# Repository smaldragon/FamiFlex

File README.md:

# FamiFlex

> Note: This project is currently in a prototype beta state, use at own risk

This is the repo for the FF1 (aka FamiFlex) famicom/famiclone homebrew mapper, more info is avaliable at:

https://smaldragon.github.io/blog/famiflex.html

* **kicad** - contains the original Kicad Files
* **python** - scripts to help with generating rom files for burning
* **gerbers** - `.zip` files for production with JLCPcb

## Changelog

### v0b

* Changed ROMS to smd PLCC sockets, to better fit cart shells
* Adjusted dimensions of PCB to better fit cart shells

### v0a

Initial Version

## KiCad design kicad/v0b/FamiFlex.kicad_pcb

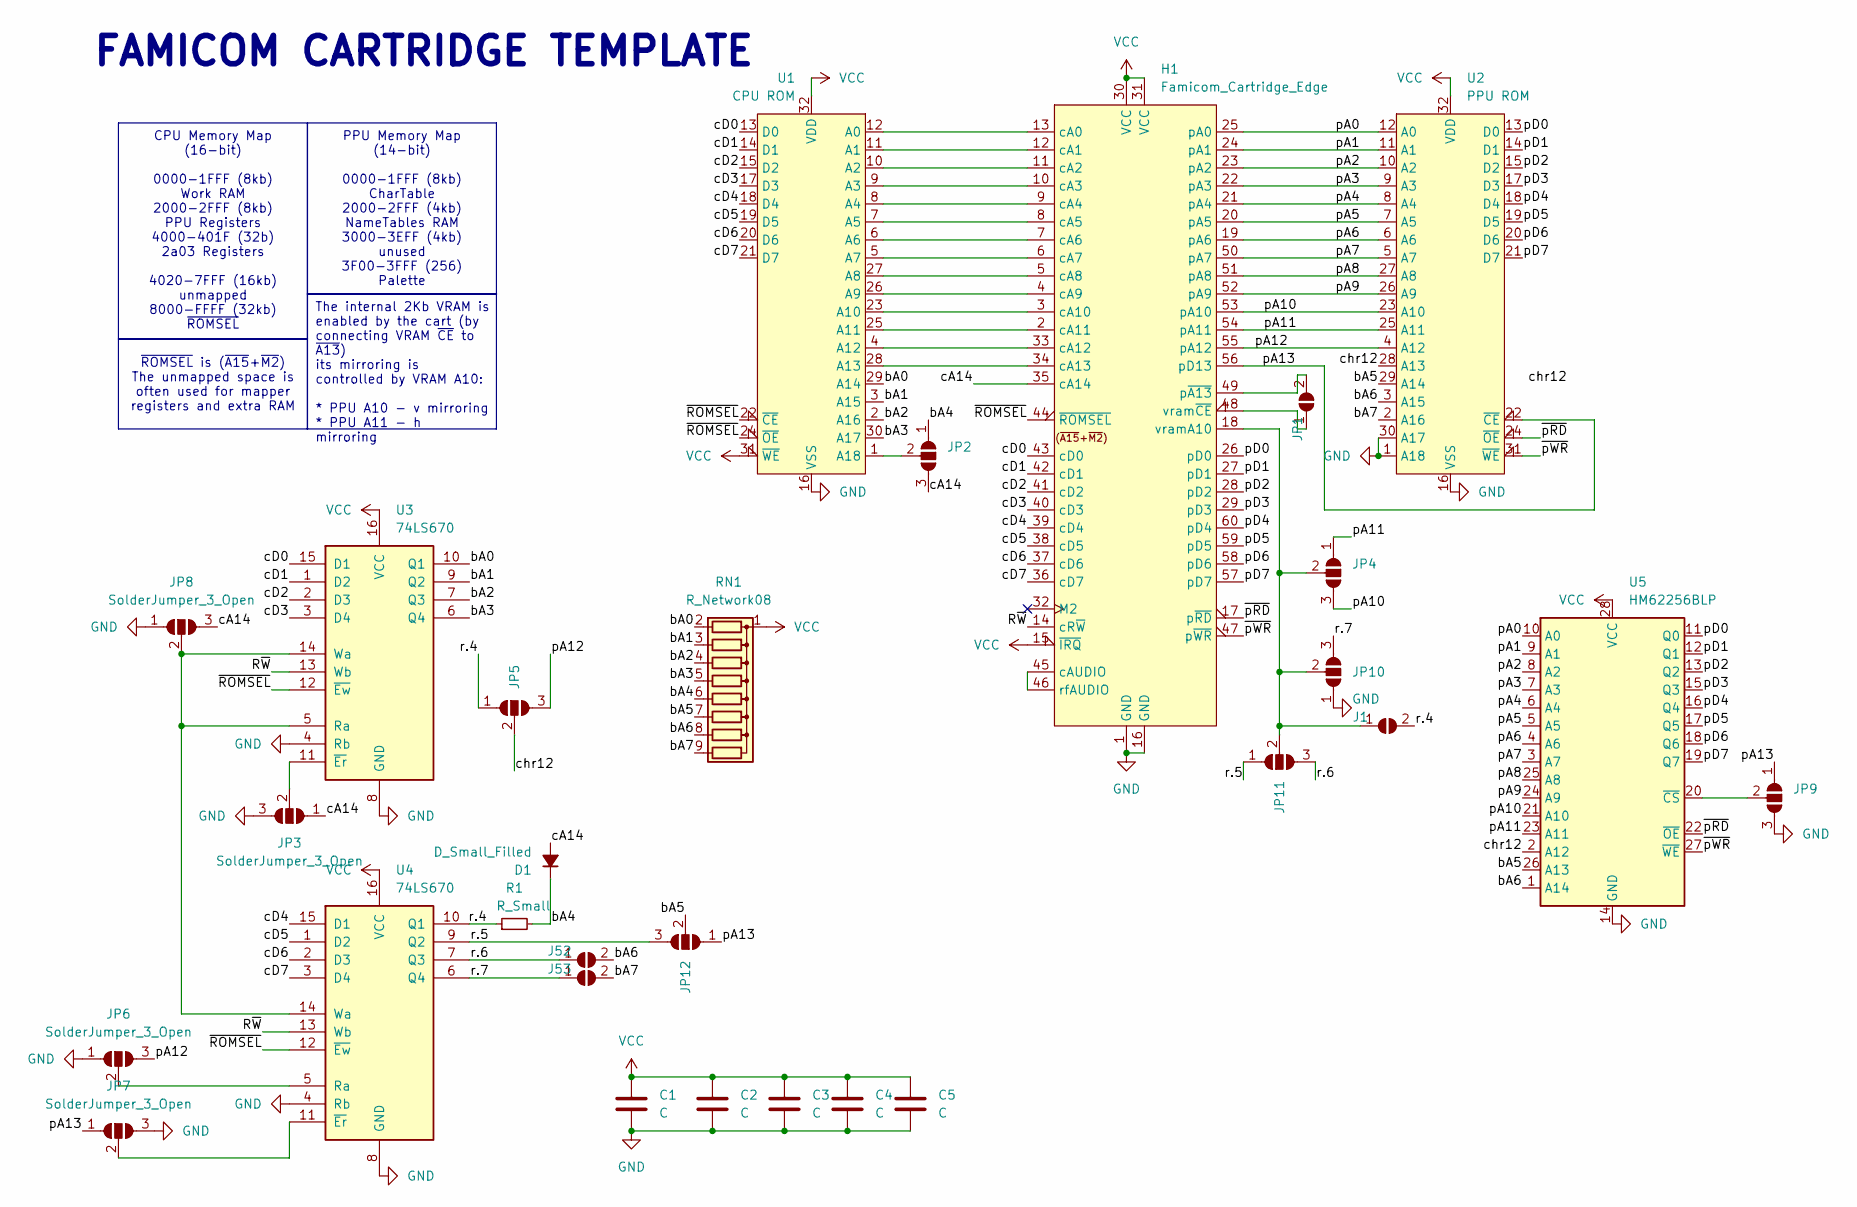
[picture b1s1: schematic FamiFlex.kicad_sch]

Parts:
C1, C2, C3, C4, C5: C; C_0805_2012Metric_Pad1.18x1.45mm_HandSolder
D1: D_Small_Filled; D_DO-41_SOD81_P2.54mm_Vertical_KathodeUp
H1: Famicom_Cartridge_Edge; Famicom Cartridge Edge Connector (long legs)
J1, J52, J53: SolderJumper_2_Open; SolderJumper-2_P1.3mm_Open_RoundedPad1.0x1.5mm
JP1: SolderJumper_2_Open; SolderJumper-2_P1.3mm_Open_RoundedPad1.0x1.5mm
JP2, JP3, JP4, JP5, JP6, JP7, JP8, JP9, JP10, JP11, JP12: SolderJumper_3_Open; SolderJumper-3_P1.3mm_Open_RoundedPad1.0x1.5mm
R1: R_Small; R_0805_2012Metric_Pad1.15x1.40mm_HandSolder
RN1: R_Network08; R_Array_SIP9
U1: CPU ROM; PLCC-32_SMD-Socket
U2: PPU ROM; PLCC-32_SMD-Socket
U3, U4: 74LS670; DIP-16_W7.62mm_Socket
U5: HM62256BLP; DIP-28_W15.24mm_Socket

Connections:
/R~W: H1.14 (cR~W), U3.13 (Wb), U4.13 (Wb)
/bA0: RN1.2 (R1), U1.29 (A14), U3.10 (Q1)
/bA1: RN1.3 (R2), U1.3 (A15), U3.9 (Q2)
/bA2: RN1.4 (R3), U1.2 (A16), U3.7 (Q3)
/bA3: RN1.5 (R4), U1.30 (A17), U3.6 (Q4)
/bA4: D1.1 (K), JP2.1 (A), R1.2, RN1.6 (R5)
/bA5: JP12.2 (C), RN1.7 (R6), U2.29 (A14), U5.26 (A13)
/bA6: J52.2 (B), RN1.8 (R7), U2.3 (A15), U5.1 (A14)
/bA7: J53.2 (B), RN1.9 (R8), U2.2 (A16)
/cA14: D1.2 (A), H1.35 (cA14), JP2.3 (B), JP3.1 (A), JP8.3 (B)
/cD0: H1.43 (cD0), U1.13 (D0), U3.15 (D1)
/cD1: H1.42 (cD1), U1.14 (D1), U3.1 (D2)
/cD2: H1.41 (cD2), U1.15 (D2), U3.2 (D3)
/cD3: H1.40 (cD3), U1.17 (D3), U3.3 (D4)
/cD4: H1.39 (cD4), U1.18 (D4), U4.15 (D1)
/cD5: H1.38 (cD5), U1.19 (D5), U4.1 (D2)
/cD6: H1.37 (cD6), U1.20 (D6), U4.2 (D3)
/cD7: H1.36 (cD7), U1.21 (D7), U4.3 (D4)
/chr12: JP5.2 (C), U2.28 (A13), U5.2 (A12)
/pA0: H1.25 (pA0), U2.12 (A0), U5.10 (A0)
/pA1: H1.24 (pA1), U2.11 (A1), U5.9 (A1)
/pA2: H1.23 (pA2), U2.10 (A2), U5.8 (A2)
/pA3: H1.22 (pA3), U2.9 (A3), U5.7 (A3)
/pA4: H1.21 (pA4), U2.8 (A4), U5.6 (A4)
/pA5: H1.20 (pA5), U2.7 (A5), U5.5 (A5)
/pA6: H1.19 (pA6), U2.6 (A6), U5.4 (A6)
/pA7: H1.50 (pA7), U2.5 (A7), U5.3 (A7)
/pA8: H1.51 (pA8), U2.27 (A8), U5.25 (A8)
/pA9: H1.52 (pA9), U2.26 (A9), U5.24 (A9)
/pA10: H1.53 (pA10), JP4.3 (B), U2.23 (A10), U5.21 (A10)
/pA11: H1.54 (pA11), JP4.1 (A), U2.25 (A11), U5.23 (A11)
/pA12: H1.55 (pA12), JP5.3 (B), JP6.3 (B), U2.4 (A12)
/pA13: H1.56 (pD13), JP7.1 (A), JP9.1 (A), JP12.1 (A), U2.22 (~CE)
/pD0: H1.26 (pD0), U2.13 (D0), U5.11 (Q0)
/pD1: H1.27 (pD1), U2.14 (D1), U5.12 (Q1)
/pD2: H1.28 (pD2), U2.15 (D2), U5.13 (Q2)
/pD3: H1.29 (pD3), U2.17 (D3), U5.15 (Q3)
/pD4: H1.60 (pD4), U2.18 (D4), U5.16 (Q4)
/pD5: H1.59 (pD5), U2.19 (D5), U5.17 (Q5)
/pD6: H1.58 (pD6), U2.20 (D6), U5.18 (Q6)
/pD7: H1.57 (pD7), U2.21 (D7), U5.19 (Q7)
/r.4: J1.2 (B), JP5.1 (A), R1.1, U4.10 (Q1)
/r.5: JP11.1 (A), JP12.3 (B), U4.9 (Q2)
/r.6: J52.1 (A), JP11.3 (B), U4.7 (Q3)
/r.7: J53.1 (A), JP10.3 (B), U4.6 (Q4)
/~ROMSEL: H1.44 (~ROMSEL), U1.22 (~CE), U1.24 (~OE), U3.12 (~Ew), U4.12 (~Ew)
/~pRD: H1.17 (p~RD), U2.24 (~OE), U5.22 (~OE)
/~pWR: H1.47 (p~WR), U2.31 (~WE), U5.27 (~WE)
GND: C1.2, C2.2, C3.2, C4.2, C5.2, H1.1 (GND), H1.16 (GND), JP3.3 (B), JP6.1 (A), JP7.3 (B), JP8.1 (A), JP9.3 (B), JP10.1 (A), U1.16 (VSS), U2.1 (A18), U2.16 (VSS), U2.30 (A17), U3.4 (Rb), U3.8 (GND), U4.4 (Rb), U4.8 (GND), U5.14 (GND)
unnamed: H1.13 (cA0), U1.12 (A0)
unnamed: H1.12 (cA1), U1.11 (A1)
unnamed: H1.11 (cA2), U1.10 (A2)
unnamed: H1.10 (cA3), U1.9 (A3)
unnamed: H1.9 (cA4), U1.8 (A4)
unnamed: H1.8 (cA5), U1.7 (A5)
unnamed: H1.7 (cA6), U1.6 (A6)
unnamed: H1.6 (cA7), U1.5 (A7)
unnamed: H1.5 (cA8), U1.27 (A8)
unnamed: H1.4 (cA9), U1.26 (A9)
unnamed: H1.3 (cA10), U1.23 (A10)
unnamed: H1.2 (cA11), U1.25 (A11)
unnamed: H1.33 (cA12), U1.4 (A12)
unnamed: H1.34 (cA13), U1.28 (A13)
unnamed: H1.45 (cAUDIO), H1.46 (rfAUDIO)
unnamed: H1.49 (p~A13), JP1.2 (B)
unnamed: H1.18 (vramA10), J1.1 (A), JP4.2 (C), JP10.2 (C), JP11.2 (C)
unnamed: H1.48 (vram~CE), JP1.1 (A)
unnamed: JP2.2 (C), U1.1 (A18)
unnamed: JP3.2 (C), U3.11 (~Er)
unnamed: JP6.2 (C), U4.5 (Ra)
unnamed: JP7.2 (C), U4.11 (~Er)
unnamed: JP8.2 (C), U3.5 (Ra), U3.14 (Wa), U4.14 (Wa)
unnamed: JP9.2 (C), U5.20 (~CS)
VCC: C1.1, C2.1, C3.1, C4.1, C5.1, H1.15 (~IRQ), H1.30 (VCC), H1.31 (VCC), RN1.1 (common), U1.31 (~WE), U1.32 (VDD), U2.32 (VDD), U3.16 (VCC), U4.16 (VCC), U5.28 (VCC)

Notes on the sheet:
PPU Memory Map (14-bit) 0000-1FFF (8kb) CharTable 2000-2FFF (4kb) NameTables RAM 3000-3EFF (4kb) unused 3F00-3FFF (256) Palette
CPU Memory Map (16-bit) 0000-1FFF (8kb) Work RAM 2000-2FFF (8kb) PPU Registers 4000-401F (32b) 2a03 Registers 4020-7FFF (16kb) unmapped 8000-FFFF (32kb) ~{ROMSEL}
~{ROMSEL} is (~{A15}+~{M2}) The unmapped space is often used for mapper registers and extra RAM
The internal 2Kb VRAM is enabled by the cart (by connecting VRAM ~{CE} to ~{A13}) its mirroring is controlled by VRAM A10: * PPU A10 - v mirroring * PPU A11 - h mirroring
FAMICOM CARTRIDGE TEMPLATE

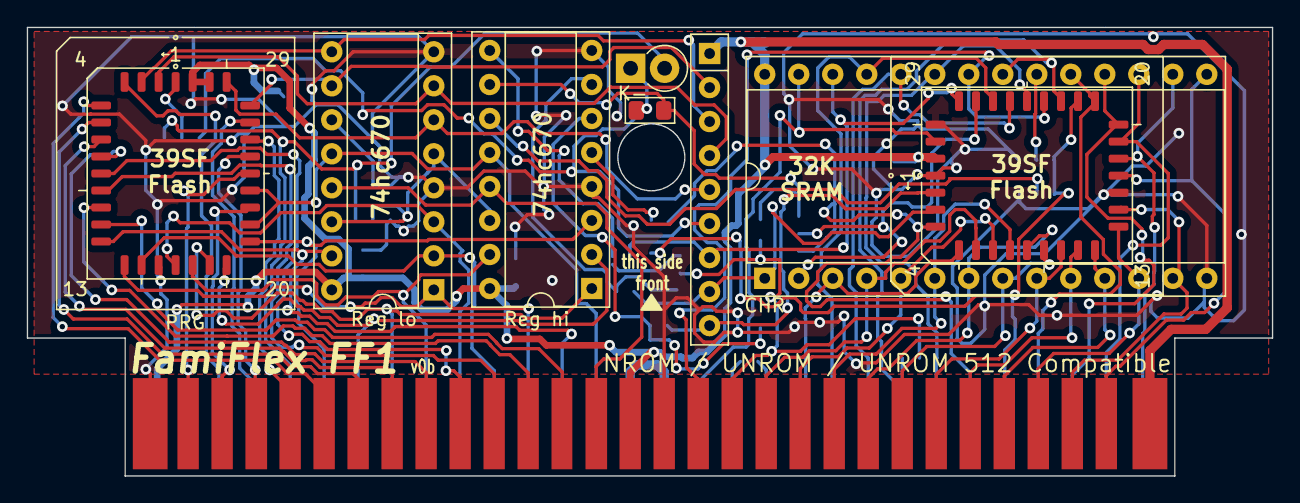
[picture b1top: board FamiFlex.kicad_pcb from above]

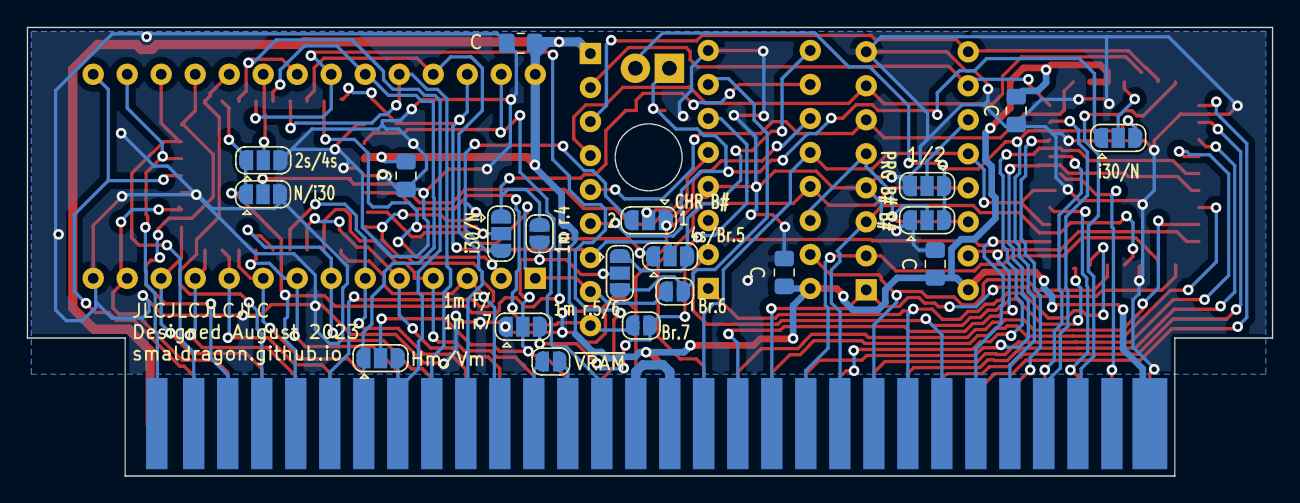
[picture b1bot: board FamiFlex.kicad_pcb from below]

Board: 2 copper layers, 93.0 x 33.5 mm, 29 parts (20 on the bottom side), 74 nets.

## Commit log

2023-12-10 fix unrom converter script
